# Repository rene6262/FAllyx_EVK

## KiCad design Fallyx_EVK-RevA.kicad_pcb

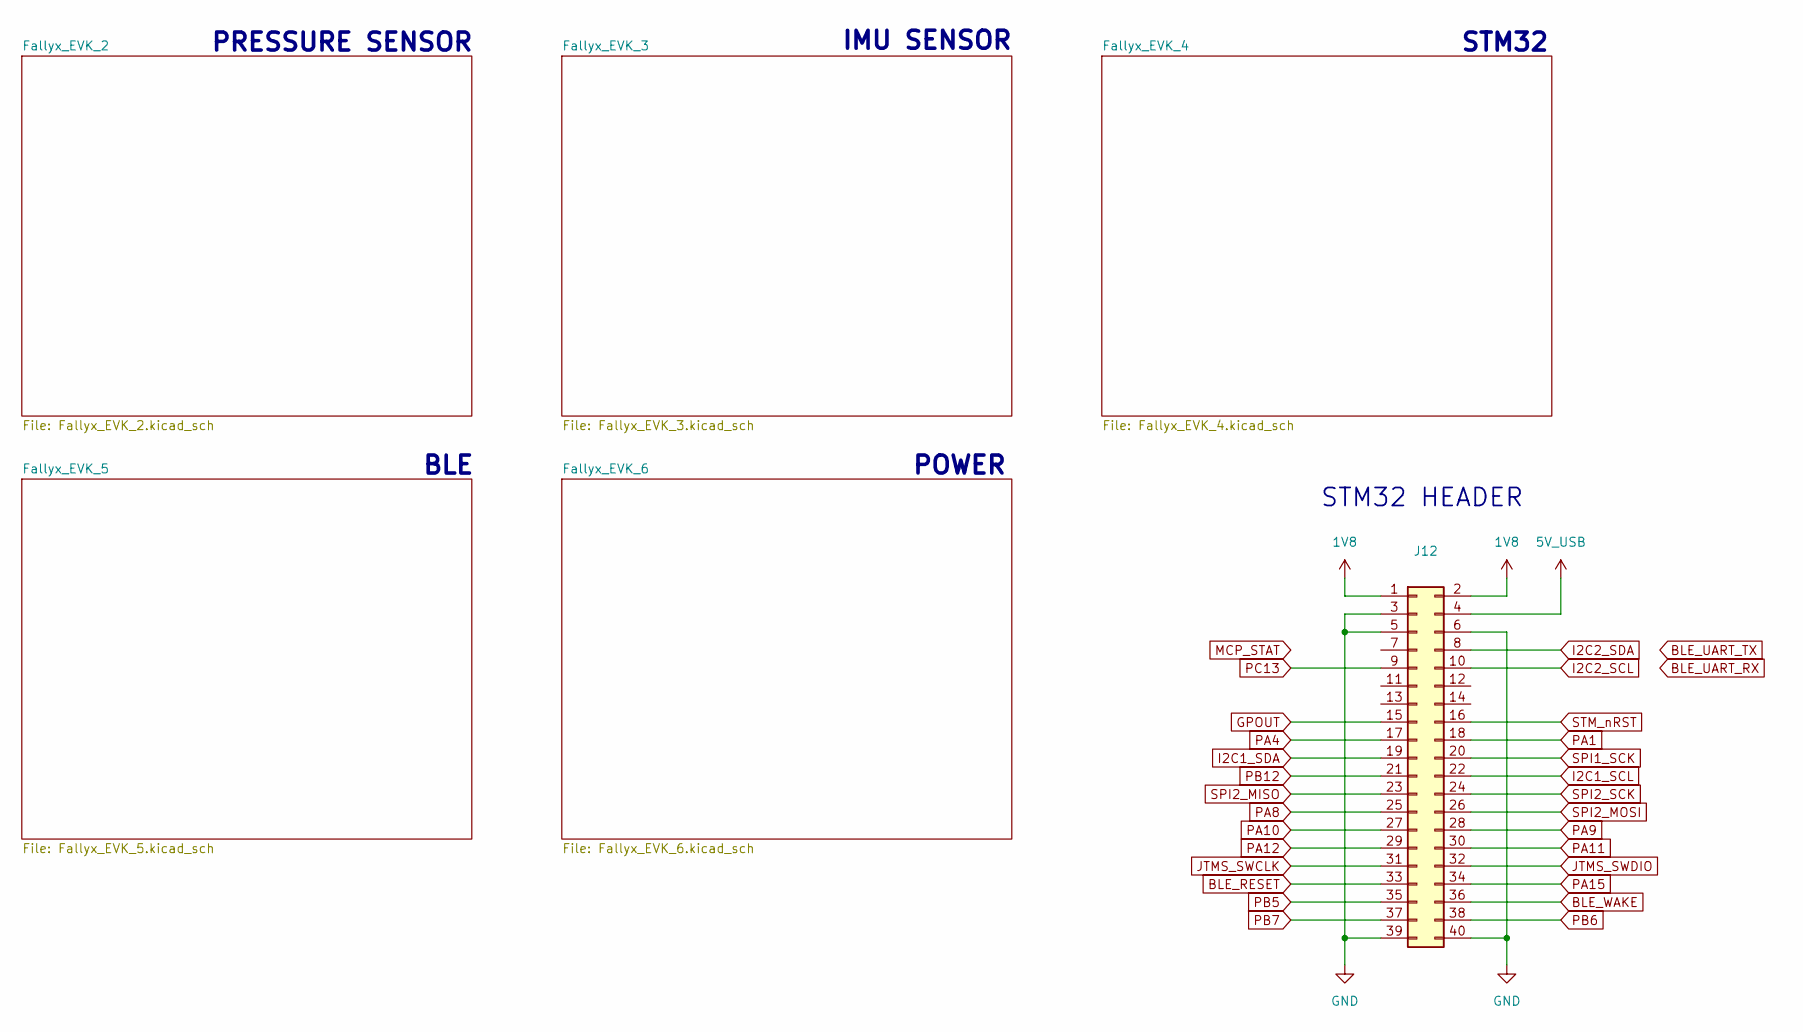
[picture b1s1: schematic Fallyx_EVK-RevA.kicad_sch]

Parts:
J12: Conn_02x20_Odd_Even; PinHeader_2x20_P2.54mm_Vertical

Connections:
1V8: J12.1, J12.2; also elsewhere on the board
5V_USB: J12.4; also elsewhere on the board
BLE_RESET: J12.33; also elsewhere on the board
BLE_UART_RX: J12.10; also elsewhere on the board
BLE_UART_TX: J12.8; also elsewhere on the board
BLE_WAKE: J12.36; also elsewhere on the board
GND: J12.3, J12.5, J12.6, J12.39, J12.40; also elsewhere on the board
GPOUT: J12.15; also elsewhere on the board
I2C1_SCL: J12.22; also elsewhere on the board
I2C1_SDA: J12.19; also elsewhere on the board
JTMS_SWCLK: J12.31; also elsewhere on the board
JTMS_SWDIO: J12.32; also elsewhere on the board
PA1: J12.18; also elsewhere on the board
PA4: J12.17; also elsewhere on the board
PA8: J12.25; also elsewhere on the board
PA9: J12.28; also elsewhere on the board
PA10: J12.27; also elsewhere on the board
PA11: J12.30; also elsewhere on the board
PA12: J12.29; also elsewhere on the board
PA15: J12.34; also elsewhere on the board
PB5: J12.35; also elsewhere on the board
PB6: J12.38; also elsewhere on the board
PB7: J12.37; also elsewhere on the board
PB12: J12.21; also elsewhere on the board
PC13: J12.9; also elsewhere on the board
SPI1_SCK: J12.20; also elsewhere on the board
SPI2_MISO: J12.23; also elsewhere on the board
SPI2_MOSI: J12.26; also elsewhere on the board
SPI2_SCK: J12.24; also elsewhere on the board
STM_nRST: J12.16; also elsewhere on the board

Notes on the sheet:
STM32 HEADER
BLE
POWER
STM32
IMU SENSOR
PRESSURE SENSOR

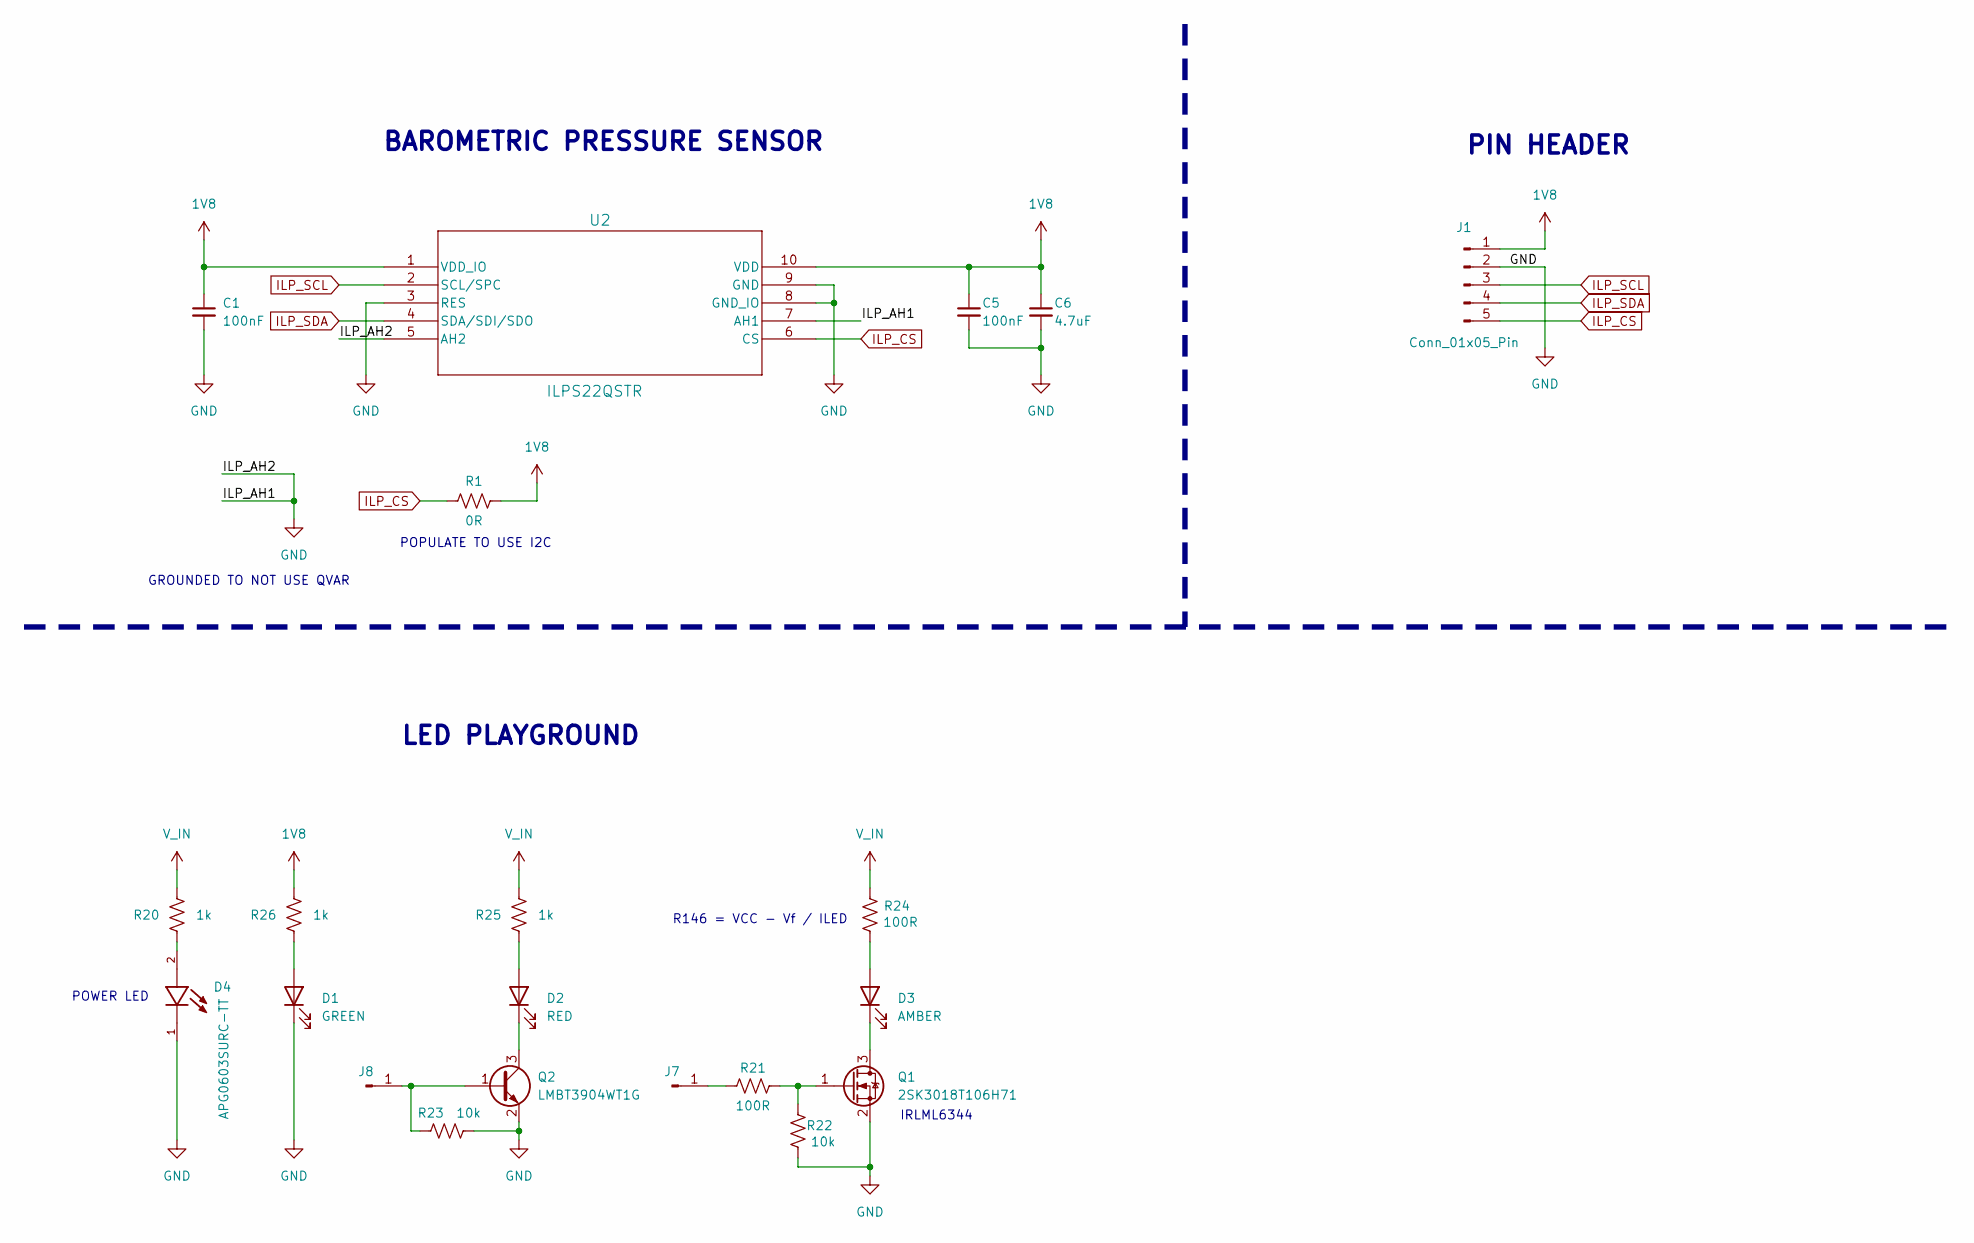
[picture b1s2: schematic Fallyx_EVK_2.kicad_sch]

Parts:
C1, C5: 100nF; C_0603_1608Metric
C6: 4.7uF; C_0603_1608Metric
D1: GREEN; LED_0603_1608Metric
D2: RED; LED_0603_1608Metric
D3: AMBER; LED_0603_1608Metric
D4: APG0603SURC-TT; LED_APG0603SURC-TT; PARTREV V.9B
J1: Conn_01x05_Pin; PinHeader_1x05_P2.54mm_Vertical
J7, J8: Conn_01x01_Pin; PinHeader_1x01_P2.54mm_Vertical
Q1: 2SK3018T106H71; SOT-323_SC-70
Q2: LMBT3904WT1G; SOT-23
R1: 0R; R_0805_2012Metric
R20, R25, R26: 1k; R_0402_1005Metric
R21, R24: 100R; R_0402_1005Metric
R22, R23: 10k; R_0402_1005Metric
U2: ILPS22QSTR; HLGA_10L_STM

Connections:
1V8: C1.1, C5.1, C6.1, J1.1, R1.2, R26.1, U2.1 (VDD_IO), U2.10 (VDD); also elsewhere on the board
GND: C1.2, C5.2, C6.2, D1.1 (K), D4.1, J1.2, Q1.2 (S), Q2.2 (E), R22.2, R23.1, U2.3 (RES), U2.5 (AH2), U2.7 (AH1), U2.8 (GND_IO), U2.9 (GND); also elsewhere on the board
ILP_CS: J1.5, R1.1, U2.6 (CS)
ILP_SCL: J1.3, U2.2 (SCL/SPC)
ILP_SDA: J1.4, U2.4 (SDA/SDI/SDO)
unnamed: D1.2 (A), R26.2
unnamed: D2.2 (A), R25.2
unnamed: D2.1 (K), Q2.3 (C)
unnamed: D3.2 (A), R24.2
unnamed: D3.1 (K), Q1.3 (D)
unnamed: D4.2, R20.2
unnamed: J7.1, R21.2
unnamed: J8.1, Q2.1 (B), R23.2
unnamed: Q1.1 (G), R21.1, R22.1
V_IN: R20.1, R24.1, R25.1; also elsewhere on the board

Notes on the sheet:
GROUNDED TO NOT USE QVAR
PIN HEADER
POPULATE TO USE I2C
IRLML6344
BAROMETRIC PRESSURE SENSOR
LED PLAYGROUND
POWER LED
R146 = VCC - Vf / ILED

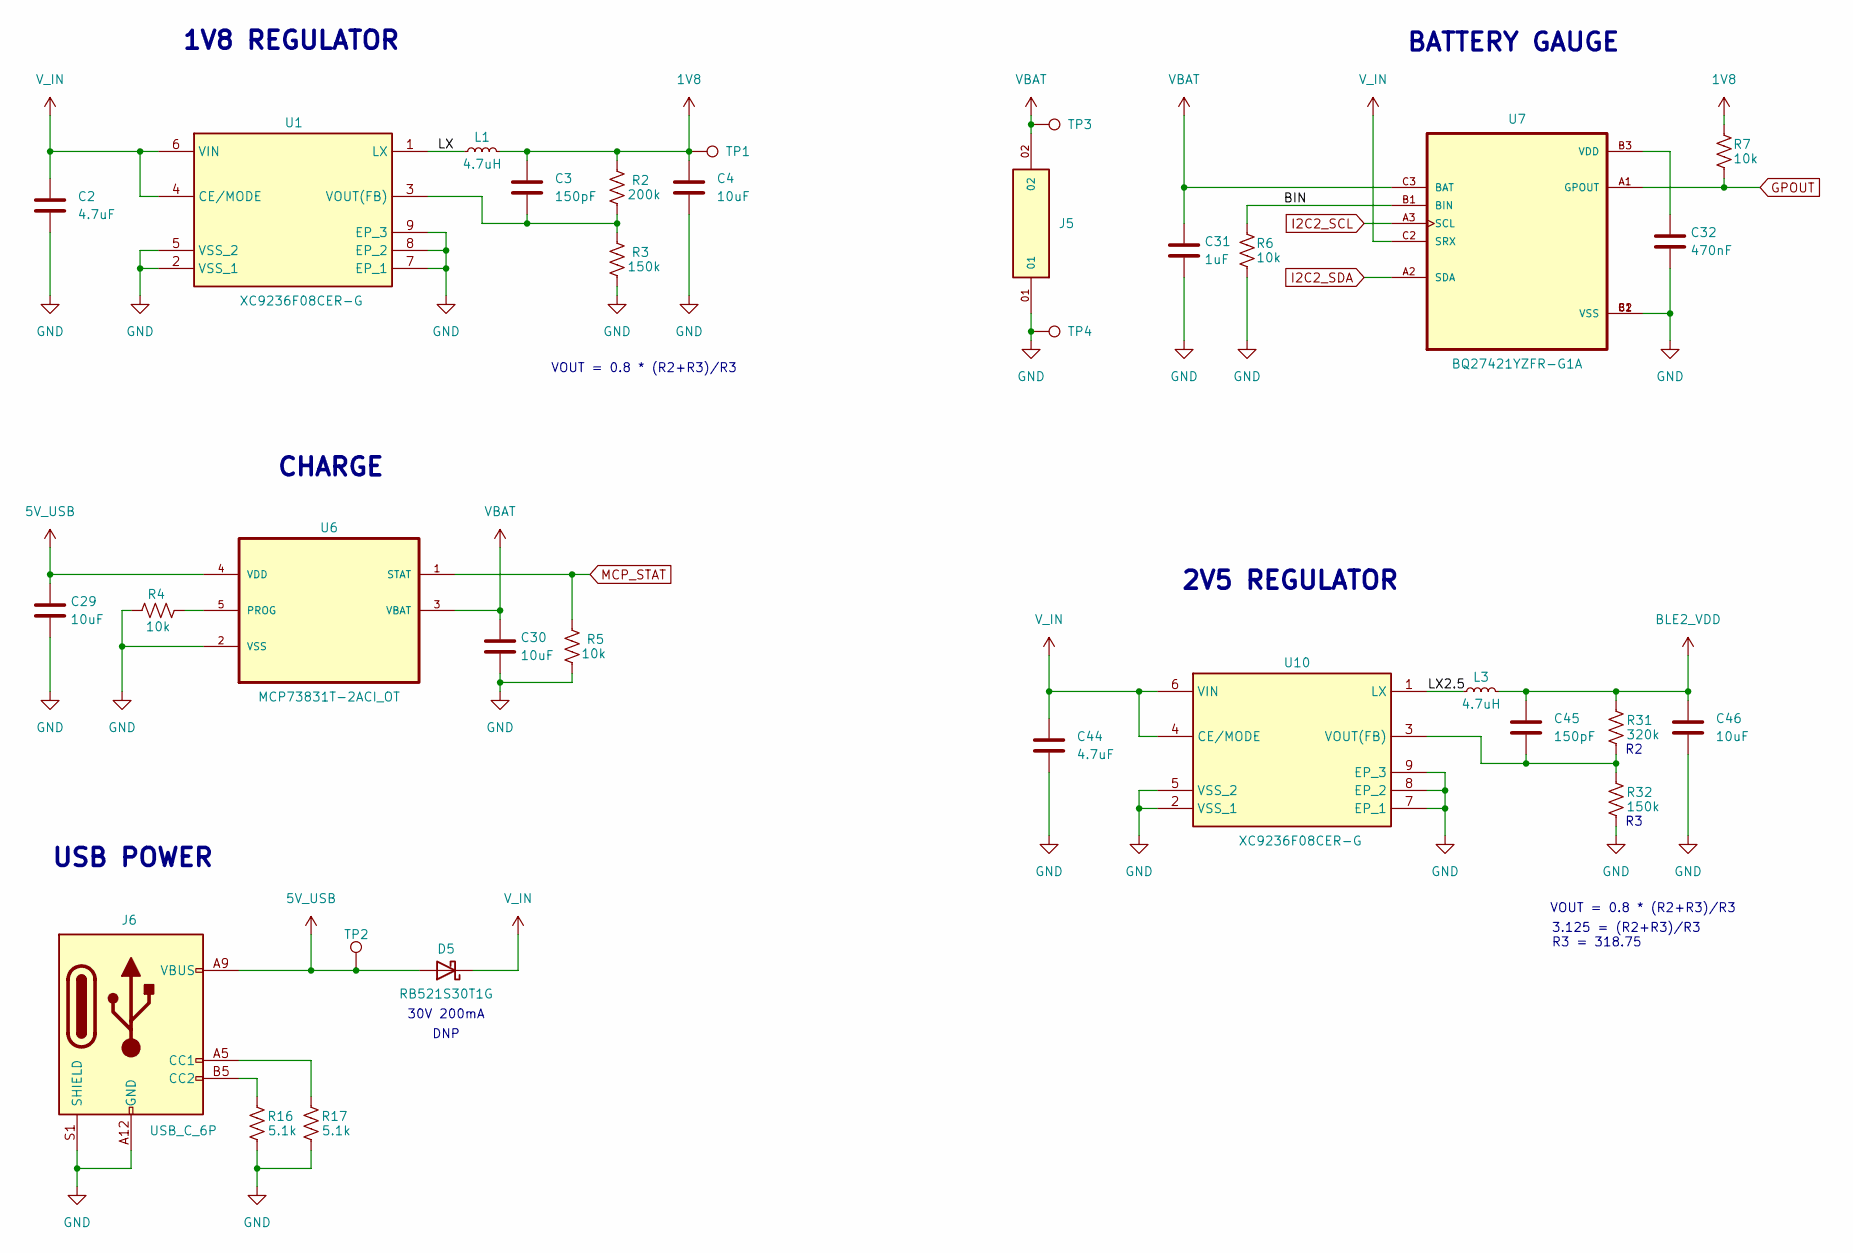
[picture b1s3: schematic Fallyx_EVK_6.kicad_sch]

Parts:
C2, C44: 4.7uF; C_0603_1608Metric
C3, C45: 150pF; C_0603_1608Metric
C4, C46: 10uF; C_0805_2012Metric
C29, C30: 10uF; C_0402_1005Metric
C31: 1uF; C_0402_1005Metric
C32: 470nF; C_0402_1005Metric
D5: RB521S30T1G; DIOM168X70N
J5: MTSW-101-X-X-D-X; SAMTEC_MTSW-101-X-X-D-X; PARTREV A
J6: USB_C_6P; USB_C_Receptacle_GCT_USB4135-GF-A_6P_TopMnt_Horizontal
L1, L3: 4.7uH; IND_TAIYO_NR3015_TAY
R2: 200k; R_0402_1005Metric
R3, R32: 150k; R_0402_1005Metric
R4, R5, R6, R7: 10k; R_0402_1005Metric
R16, R17: 5.1k; R_0402_1005Metric
R31: 320k; R_0402_1005Metric
TP1, TP2, TP3, TP4: TestPoint; TestPoint_Pad_D1.5mm
U1, U10: XC9236F08CER-G; XC9236F08CERG; Mouser Part Number 865-XC9236F08CER-G
U6: MCP73831T-2ACI_OT; SOT95P280X145-5N; MPN MCP73831T-2ACI/OT
U7: BQ27421YZFR-G1A; IC_BQ27421YZFR-G1A

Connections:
1V8: C3.1, C4.1, L1.2, R2.2, R7.2, TP1.1; also elsewhere on the board
5V_USB: C29.1, D5.2 (A), J6.A9 (VBUS), J6.B9 (VBUS), TP2.1, U6.4 (VDD); also elsewhere on the board
/Fallyx_EVK_6/BIN: R6.2, U7.B1 (BIN)
/Fallyx_EVK_6/LX: L1.1, U1.1 (LX)
/Fallyx_EVK_6/LX2.5: L3.1, U10.1 (LX)
BLE2_VDD: C45.1, C46.1, L3.2, R31.2; also elsewhere on the board
BLE_UART_RX: U7.A3 (SCL); also elsewhere on the board
BLE_UART_TX: U7.A2 (SDA); also elsewhere on the board
GND: C2.2, C4.2, C29.2, C30.2, C31.2, C32.2, C44.2, C46.2, J5.01, J6.A12 (GND), J6.B12 (GND), J6.S1 (SHIELD), R3.1, R4.2, R5.1, R6.1, R16.1, R17.1, R32.1, TP4.1, U1.2 (VSS_1), U1.5 (VSS_2), U1.7 (EP_1), U1.8 (EP_2), U1.9 (EP_3), U6.2 (VSS), U7.B2 (VSS), U7.C1 (VSS), U10.2 (VSS_1), U10.5 (VSS_2), U10.7 (EP_1), U10.8 (EP_2), U10.9 (EP_3); also elsewhere on the board
GPOUT: R7.1, U7.A1 (GPOUT); also elsewhere on the board
MCP_STAT: R5.2, U6.1 (STAT); also elsewhere on the board
unnamed: J6.A5 (CC1), R17.2
unnamed: J6.B5 (CC2), R16.2
unnamed: C3.2, R2.1, R3.2, U1.3 (VOUT(FB))
unnamed: R4.1, U6.5 (PROG)
unnamed: C32.1, U7.B3 (VDD)
unnamed: C45.2, R31.1, R32.2, U10.3 (VOUT(FB))
VBAT: C30.1, C31.1, J5.02, TP3.1, U6.3 (VBAT), U7.C3 (BAT); also elsewhere on the board
V_IN: C2.1, C44.1, D5.1 (K), U1.4 (CE/MODE), U1.6 (VIN), U7.C2 (SRX), U10.4 (CE/MODE), U10.6 (VIN); also elsewhere on the board

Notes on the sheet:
USB POWER
VOUT = 0.8 * (R2+R3)/R3
30V 200mA
1V8 REGULATOR
DNP
BATTERY GAUGE
3.125 = (R2+R3)/R3 R3 = 318.75
CHARGE
2V5 REGULATOR

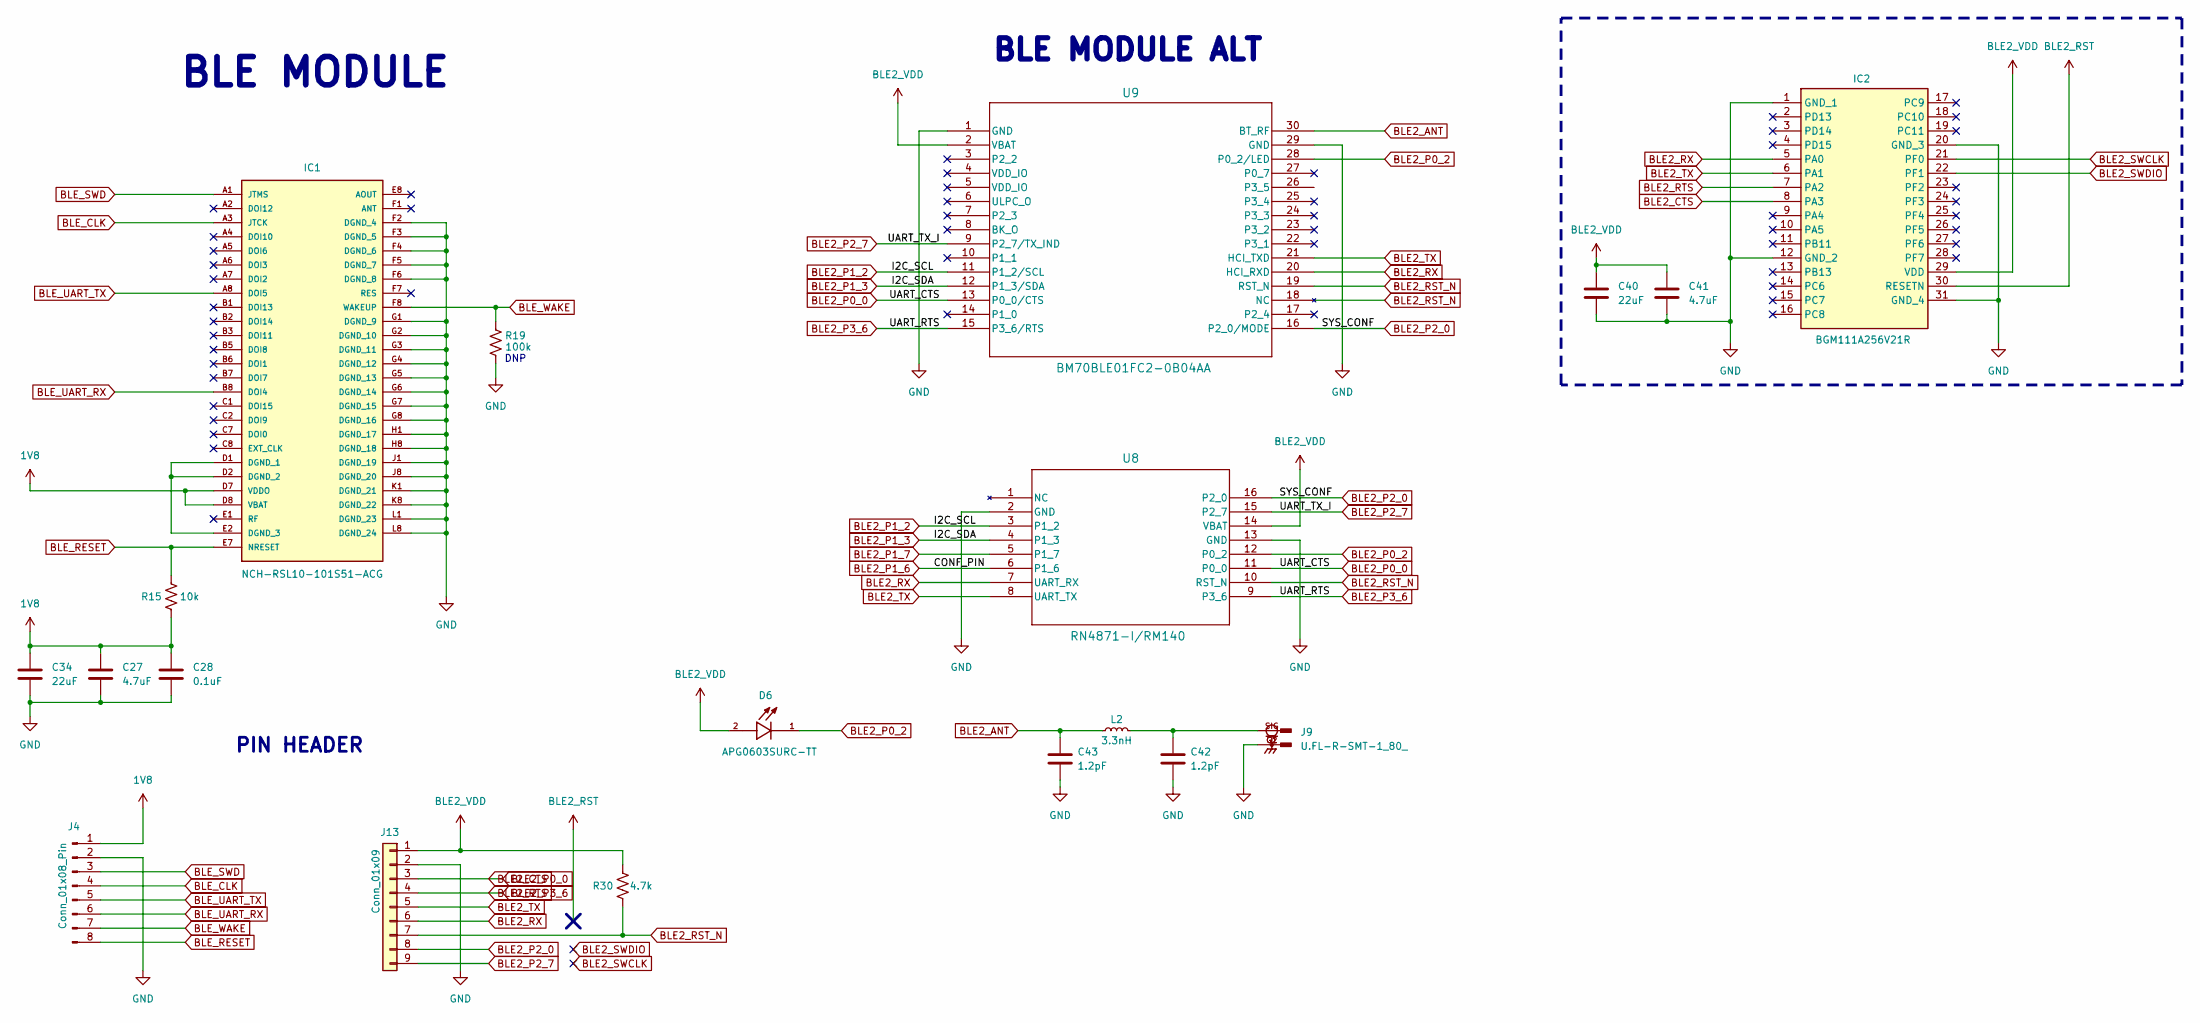
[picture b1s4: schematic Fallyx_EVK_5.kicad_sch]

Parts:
C27, C41: 4.7uF; C_0603_1608Metric
C28: 0.1uF; C_0402_1005Metric
C34, C40: 22uF; C_0603_1608Metric
C42, C43: 1.2pF; C_0402_1005Metric
D6: APG0603SURC-TT; LED_APG0603SURC-TT; PARTREV V.9B
IC1: NCH-RSL10-101S51-ACG; NCHRSL10101S51ACG; Mouser_Part_Number 863-NCHRSL1010S51ACG
IC2: BGM111A256V21R; Mouser Part Number 634-BGM111A256V21R
J4: Conn_01x08_Pin; PinHeader_1x08_P2.54mm_Vertical
J9: U.FL-R-SMT-1_80_; HIROSE_U.FL-R-SMT-1_80_; PARTREV Jul.1.2022
J13: Conn_01x09; PinHeader_1x09_P2.54mm_Vertical
L2: 3.3nH; L_0402_1005Metric
R15: 10k; R_0402_1005Metric
R19: 100k; R_0402_1005Metric
R30: 4.7k; R_0402_1005Metric
U8: RN4871-I/RM140; Microchip_RN4871
U9: BM70BLE01FC2-0B04AA; BM70BLE01FC2_MCH

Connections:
1V8: C27.1, C28.1, C34.1, IC1.D7 (VDDO), IC1.D8 (VBAT), J4.1, R15.1; also elsewhere on the board
BLE2_ANT: C43.1, L2.1, U9.30 (BT_RF)
BLE2_CTS: IC2.8 (PA3), J13.3, U8.11 (P0_0), U9.13 (P0_0/CTS)
BLE2_P0_2: D6.1, U8.12 (P0_2), U9.28 (P0_2/LED)
BLE2_P1_2: U8.3 (P1_2), U9.11 (P1_2/SCL)
BLE2_P1_3: U8.4 (P1_3), U9.12 (P1_3/SDA)
BLE2_P1_6: U8.6 (P1_6)
BLE2_P1_7: U8.5 (P1_7)
BLE2_P2_0: J13.8, U8.16 (P2_0), U9.16 (P2_0/MODE)
BLE2_P2_7: J13.9, U8.15 (P2_7), U9.9 (P2_7/TX_IND)
BLE2_P3_6: IC2.7 (PA2), J13.4, U8.9 (P3_6), U9.15 (P3_6/RTS)
BLE2_RST_N: J13.7, R30.1, U8.10 (RST_N), U9.18 (NC), U9.19 (RST_N)
BLE2_RX: IC2.5 (PA0), J13.6, U8.7 (UART_RX), U9.20 (HCI_RXD)
BLE2_TX: IC2.6 (PA1), J13.5, U8.8 (UART_TX), U9.21 (HCI_TXD)
BLE2_VDD: C40.1, C41.1, D6.2, IC2.29 (VDD), J13.1, R30.2, U8.14 (VBAT), U9.2 (VBAT); also elsewhere on the board
BLE_CLK: IC1.A3 (JTCK), J4.4
BLE_RESET: IC1.E7 (NRESET), J4.8, R15.2; also elsewhere on the board
BLE_SWD: IC1.A1 (JTMS), J4.3
BLE_UART_RX: IC1.B8 (DOI4), J4.6; also elsewhere on the board
BLE_UART_TX: IC1.A8 (DOI5), J4.5; also elsewhere on the board
BLE_WAKE: IC1.F8 (WAKEUP), J4.7, R19.2; also elsewhere on the board
GND: C27.2, C28.2, C34.2, C40.2, C41.2, C42.2, C43.2, IC1.F2 (DGND_4), IC1.F3 (DGND_5), IC1.F4 (DGND_6), IC1.F5 (DGND_7), IC1.F6 (DGND_8), IC1.G1 (DGND_9), IC1.G2 (DGND_10), IC1.G3 (DGND_11), IC1.G4 (DGND_12), IC1.G5 (DGND_13), IC1.G6 (DGND_14), IC1.G7 (DGND_15), IC1.G8 (DGND_16), IC1.H1 (DGND_17), IC1.H8 (DGND_18), IC1.J1 (DGND_19), IC1.J8 (DGND_20), IC1.K1 (DGND_21), IC1.K8 (DGND_22), IC1.L1 (DGND_23), IC1.L8 (DGND_24), IC2.1 (GND_1), IC2.12 (GND_2), IC2.20 (GND_3), IC2.31 (GND_4), J4.2, J9.G1, J9.G2, J13.2, R19.1, U8.2 (GND), U8.13 (GND), U9.1 (GND), U9.29 (GND); also elsewhere on the board
unnamed: C42.1, J9.SIG, L2.2
unnamed: IC1.D1 (DGND_1), IC1.D2 (DGND_2), IC1.E2 (DGND_3)

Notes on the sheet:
PIN HEADER
DNP
BLE MODULE
BLE MODULE ALT

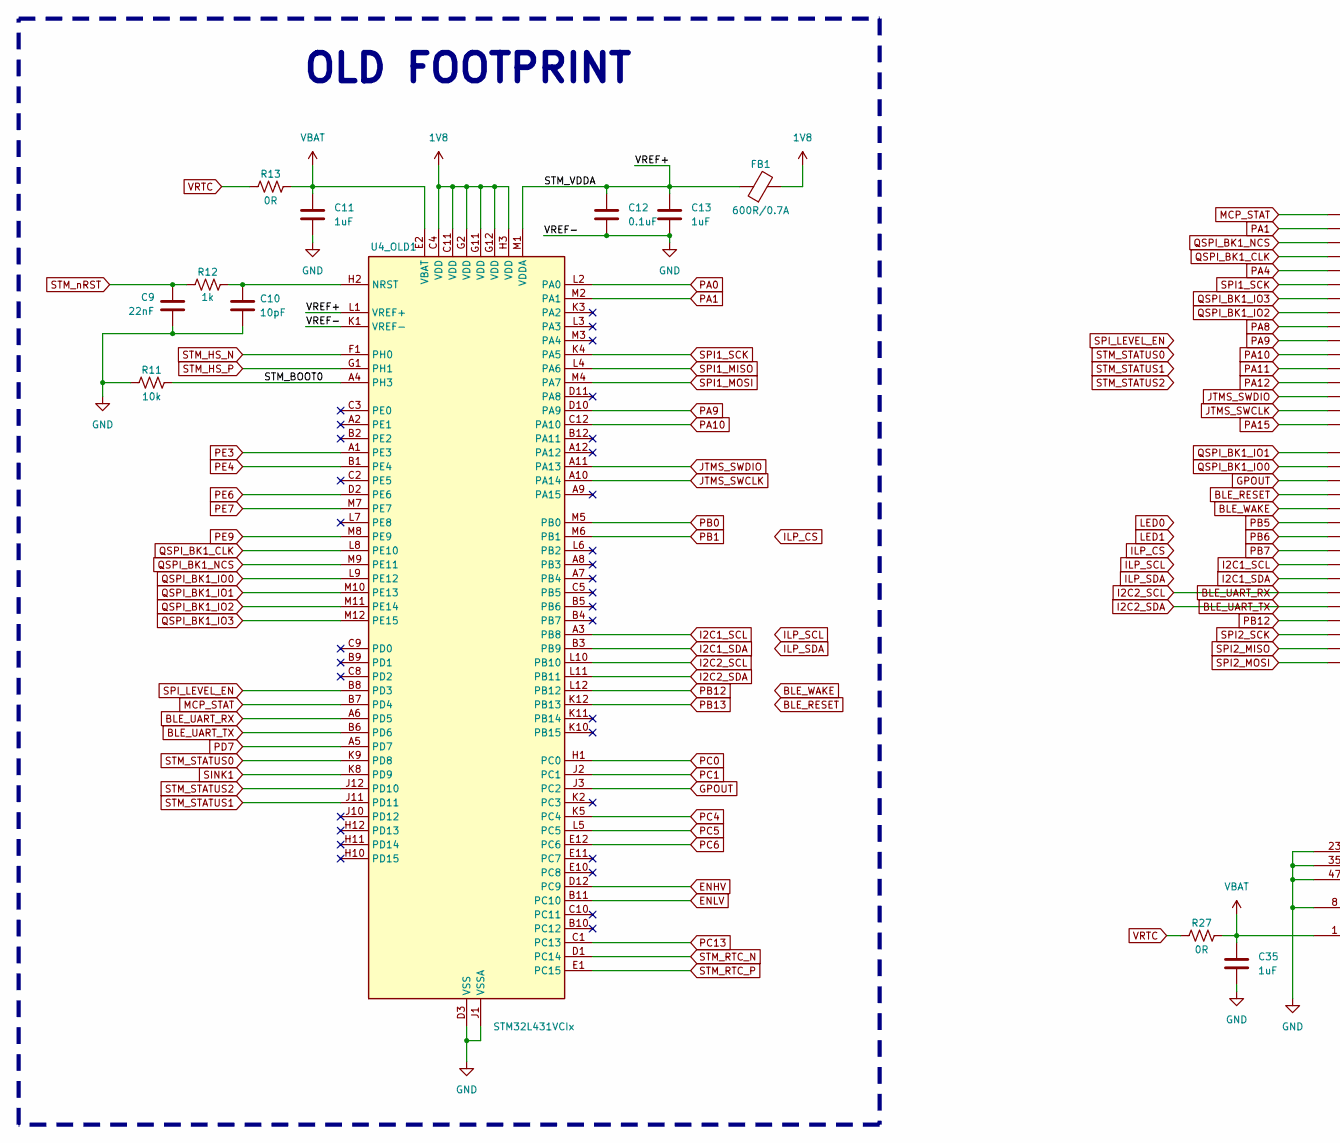
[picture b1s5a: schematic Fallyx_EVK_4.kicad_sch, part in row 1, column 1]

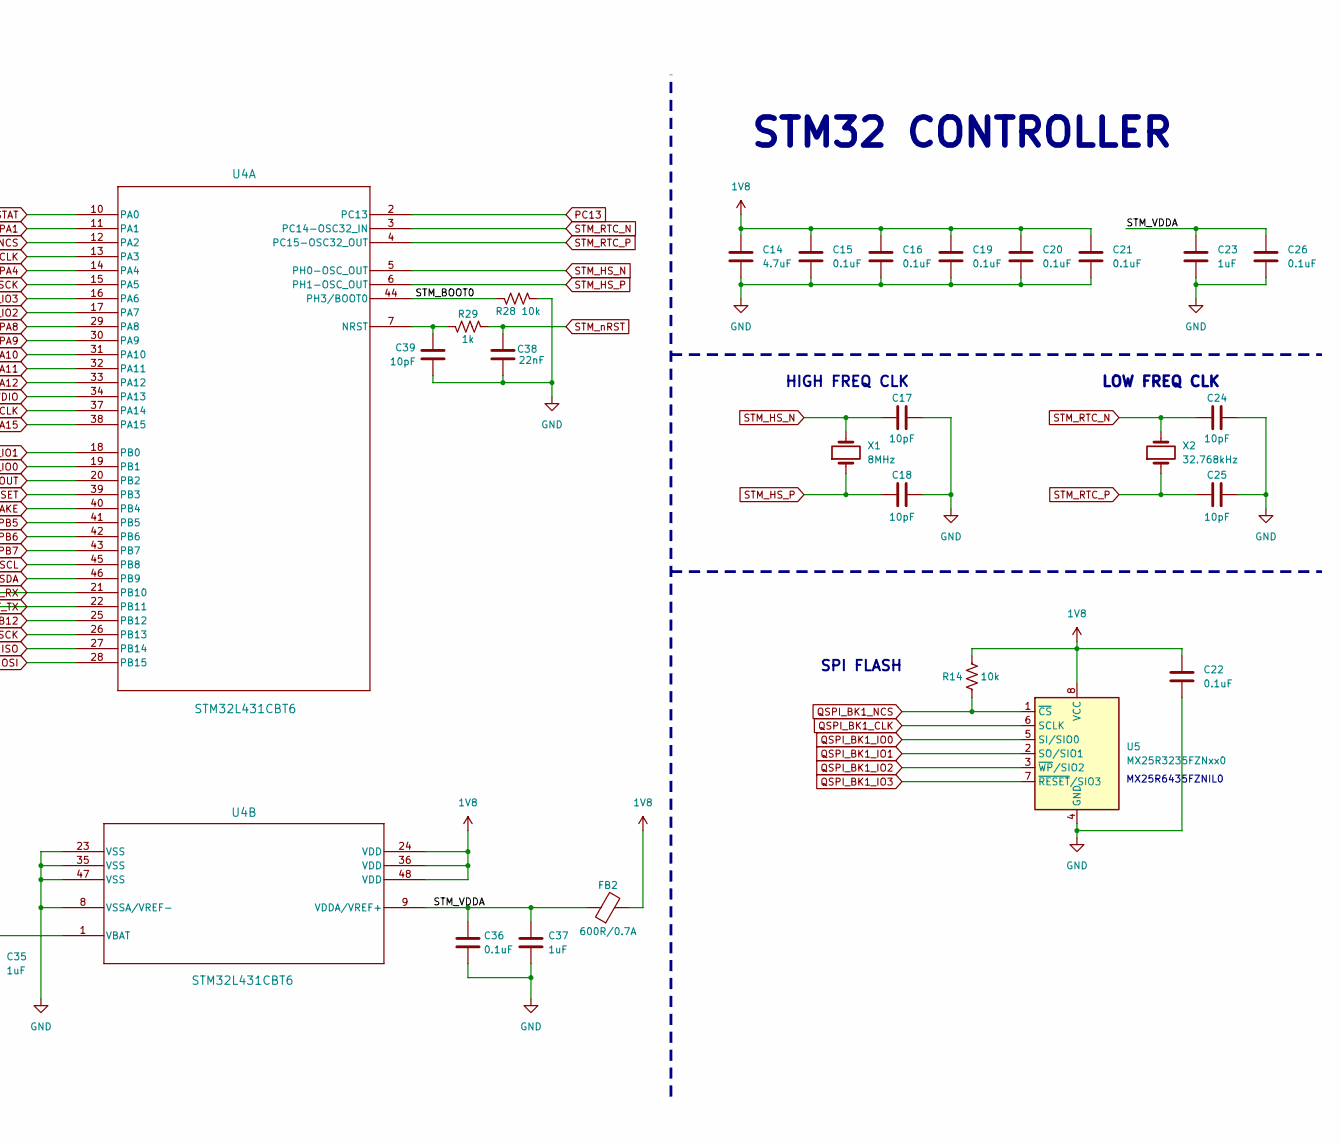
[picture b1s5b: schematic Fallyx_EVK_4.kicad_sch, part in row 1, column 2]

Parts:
C9, C38: 22nF; C_0402_1005Metric
C10, C17, C18, C24, C25, C39: 10pF; C_0402_1005Metric
C11, C13, C23, C35, C37: 1uF; C_0402_1005Metric
C12, C15, C16, C19, C20, C21, C22, C26, C36: 0.1uF; C_0402_1005Metric
C14: 4.7uF; C_0603_1608Metric
FB1: 600R/0.7A
FB2: 600R/0.7A; R_0402_1005Metric
R11, R14, R28: 10k; R_0402_1005Metric
R12, R29: 1k; R_0402_1005Metric
R13, R27: 0R; R_0805_2012Metric
U4: STM32L431CBT6; LQFP-48
U4_OLD1: STM32L431VCIx; UFBGA-100_7x7mm_Layout12x12_P0.5mm
U5: MX25R3235FZNxx0; WSON-8-1EP_6x5mm_P1.27mm_EP3.4x4mm
X1: 8MHz; XTAL_ECS-320-CDX-2094
X2: 32.768kHz; XTAL_CM9V-T1A-32.768KHZ-7PF-100PPM-TA-QC

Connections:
1V8: C14.1, C15.1, C16.1, C19.1, C20.1, C21.1, C22.1, FB1.2, FB2.2, R14.2, U4.24 (VDD), U4.36 (VDD), U4.48 (VDD), U4_OLD1.C4 (VDD), U4_OLD1.C11 (VDD), U4_OLD1.G2 (VDD), U4_OLD1.G11 (VDD), U4_OLD1.G12 (VDD), U4_OLD1.H3 (VDD), U5.8 (VCC); also elsewhere on the board
/Fallyx_EVK_4/STM_BOOT0: R11.2, R28.2, U4.44 (PH3/BOOT0), U4_OLD1.A4 (PH3)
/Fallyx_EVK_4/STM_VDDA: C12.1, C13.1, C23.1, C26.1, C36.1, C37.1, FB1.1, FB2.1, U4.9 (VDDA/VREF+), U4_OLD1.L1 (VREF+), U4_OLD1.M1 (VDDA)
BLE_RESET: U4.39 (PB3); also elsewhere on the board
BLE_UART_RX: U4.21 (PB10), U4_OLD1.A6 (PD5), U4_OLD1.L10 (PB10); also elsewhere on the board
BLE_UART_TX: U4.22 (PB11), U4_OLD1.B6 (PD6), U4_OLD1.L11 (PB11); also elsewhere on the board
BLE_WAKE: U4.40 (PB4); also elsewhere on the board
GND: C9.2, C10.2, C11.2, C12.2, C13.2, C14.2, C15.2, C16.2, C17.2, C18.2, C19.2, C20.2, C21.2, C22.2, C23.2, C24.2, C25.2, C26.2, C35.2, C36.2, C37.2, C38.2, C39.2, R11.1, R28.1, U4.8 (VSSA/VREF-), U4.23 (VSS), U4.35 (VSS), U4.47 (VSS), U4_OLD1.D3 (VSS), U4_OLD1.E3 (VSS), U4_OLD1.F2 (VSS), U4_OLD1.F11 (VSS), U4_OLD1.F12 (VSS), U4_OLD1.J1 (VSSA), U4_OLD1.K1 (VREF-), U5.4 (GND), U5.9 (GND); also elsewhere on the board
GPOUT: U4.20 (PB2), U4_OLD1.J3 (PC2); also elsewhere on the board
I2C1_SCL: U4.45 (PB8), U4_OLD1.A3 (PB8); also elsewhere on the board
I2C1_SDA: U4.46 (PB9), U4_OLD1.B3 (PB9); also elsewhere on the board
JTMS_SWCLK: U4.37 (PA14), U4_OLD1.A10 (PA14); also elsewhere on the board
JTMS_SWDIO: U4.34 (PA13), U4_OLD1.A11 (PA13); also elsewhere on the board
MCP_STAT: U4.10 (PA0), U4_OLD1.B7 (PD4); also elsewhere on the board
unnamed: C10.1, R12.2, U4_OLD1.H2 (NRST)
unnamed: C39.1, R29.2, U4.7 (NRST)
PA1: U4.11 (PA1), U4_OLD1.M2 (PA1); also elsewhere on the board
PA4: U4.14 (PA4); also elsewhere on the board
PA8: U4.29 (PA8); also elsewhere on the board
PA9: U4.30 (PA9), U4_OLD1.D10 (PA9); also elsewhere on the board
PA10: U4.31 (PA10), U4_OLD1.C12 (PA10); also elsewhere on the board
PA11: U4.32 (PA11); also elsewhere on the board
PA12: U4.33 (PA12); also elsewhere on the board
PA15: U4.38 (PA15); also elsewhere on the board
PB5: U4.41 (PB5); also elsewhere on the board
PB6: U4.42 (PB6); also elsewhere on the board
PB7: U4.43 (PB7); also elsewhere on the board
PB12: U4.25 (PB12), U4_OLD1.L12 (PB12); also elsewhere on the board
PC13: U4.2 (PC13), U4_OLD1.C1 (PC13); also elsewhere on the board
QSPI_BK1_CLK: U4.13 (PA3), U4_OLD1.L8 (PE10), U5.6 (SCLK)
QSPI_BK1_IO0: U4.19 (PB1), U4_OLD1.L9 (PE12), U5.5 (SI/SIO0)
QSPI_BK1_IO1: U4.18 (PB0), U4_OLD1.M10 (PE13), U5.2 (SO/SIO1)
QSPI_BK1_IO2: U4.17 (PA7), U4_OLD1.M11 (PE14), U5.3 (~WP/SIO2)
QSPI_BK1_IO3: U4.16 (PA6), U4_OLD1.M12 (PE15), U5.7 (~RESET/SIO3)
QSPI_BK1_NCS: R14.1, U4.12 (PA2), U4_OLD1.M9 (PE11), U5.1 (~CS)
SPI1_SCK: U4.15 (PA5), U4_OLD1.K4 (PA5); also elsewhere on the board
SPI2_MISO: U4.27 (PB14); also elsewhere on the board
SPI2_MOSI: U4.28 (PB15); also elsewhere on the board
SPI2_SCK: U4.26 (PB13); also elsewhere on the board
STM_HS_N: C17.1, U4.5 (PH0-OSC_OUT), U4_OLD1.F1 (PH0), X1.2
STM_HS_P: C18.1, U4.6 (PH1-OSC_OUT), U4_OLD1.G1 (PH1), X1.1
STM_RTC_N: C24.1, U4.3 (PC14-OSC32_IN), U4_OLD1.D1 (PC14), X2.2
STM_RTC_P: C25.1, U4.4 (PC15-OSC32_OUT), U4_OLD1.E1 (PC15), X2.1
STM_nRST: C9.1, C38.1, R12.1, R29.1; also elsewhere on the board
VBAT: C11.1, C35.1, R13.2, R27.2, U4.1 (VBAT), U4_OLD1.E2 (VBAT); also elsewhere on the board
VRTC: R13.1, R27.1

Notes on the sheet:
OLD FOOTPRINT
HIGH FREQ CLK
LOW FREQ CLK
MX25R6435FZNIL0
SPI FLASH
STM32 CONTROLLER

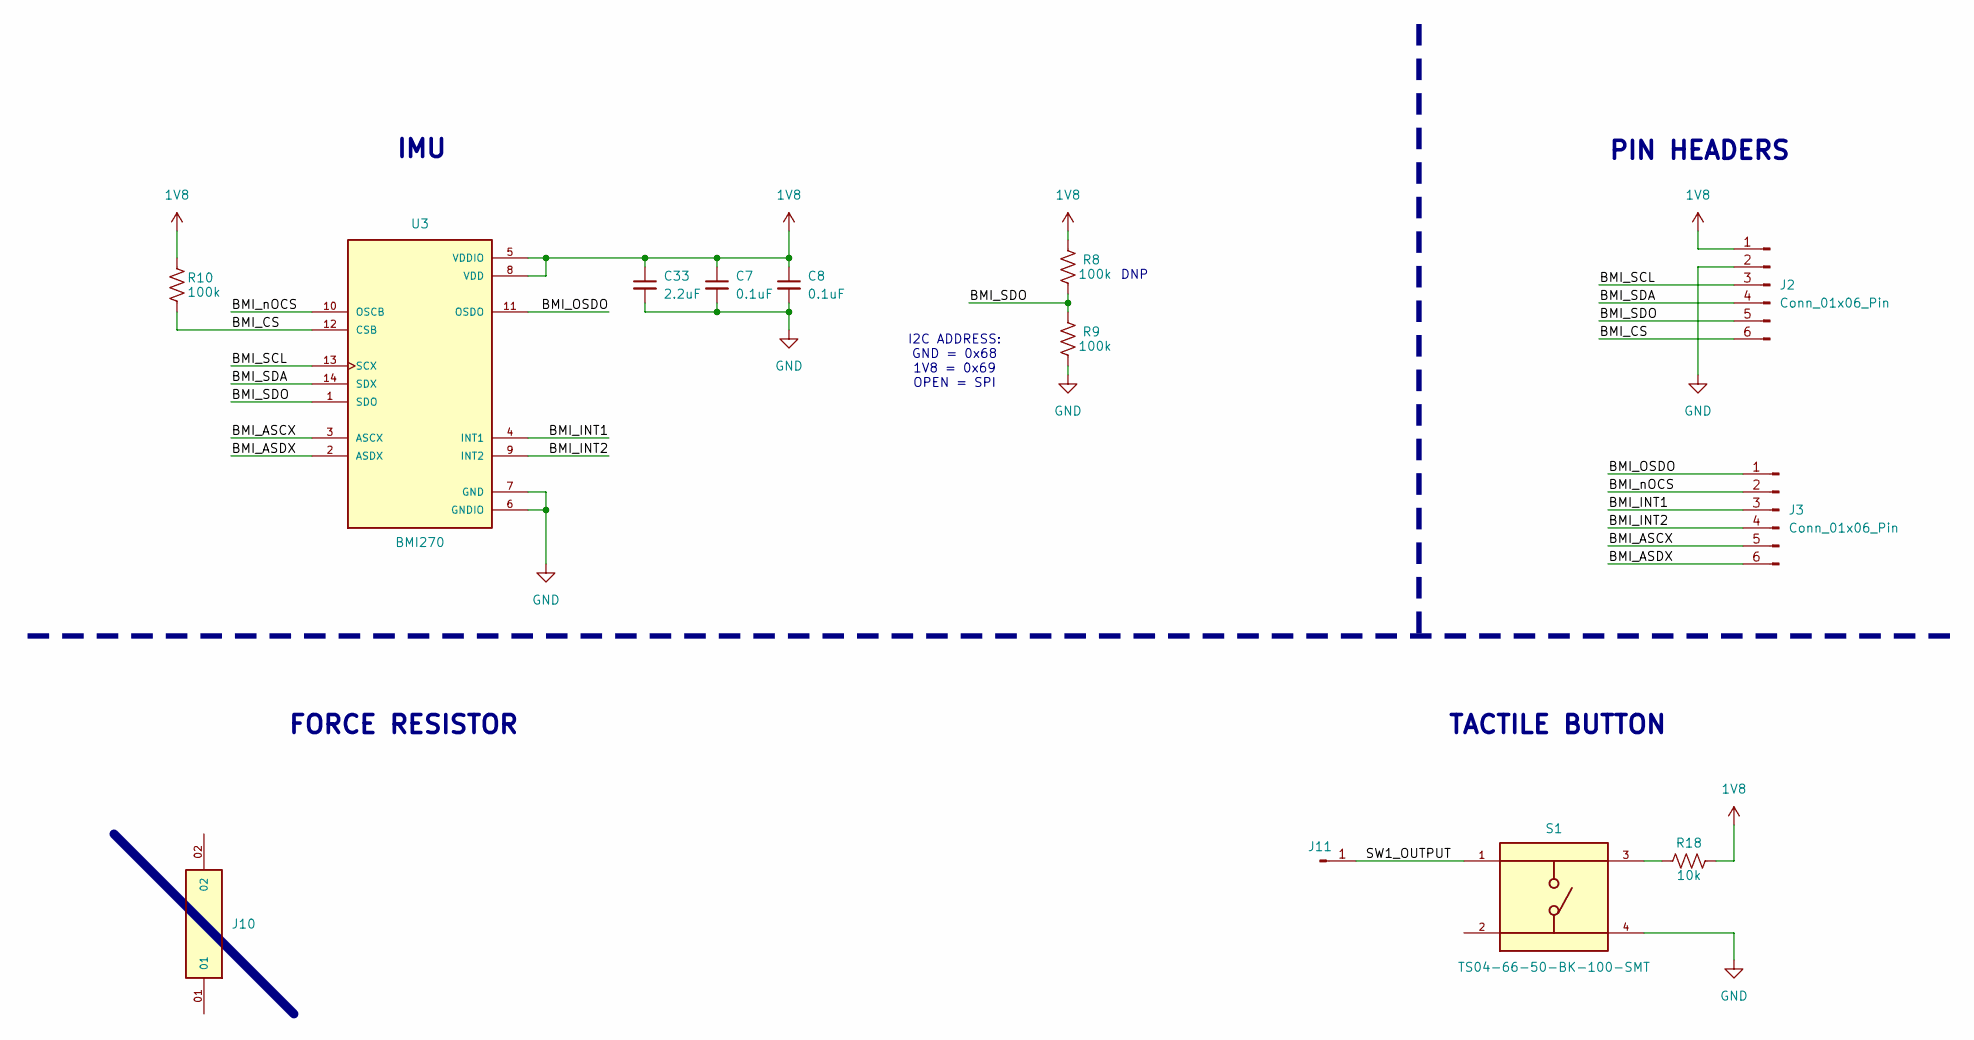
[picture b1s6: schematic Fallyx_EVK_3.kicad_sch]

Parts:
C7, C8: 0.1uF; C_0603_1608Metric
C33: 2.2uF; C_0603_1608Metric
J2, J3: Conn_01x06_Pin; PinHeader_1x06_P2.54mm_Vertical
J10: MTSW-101-X-X-D-X; SAMTEC_MTSW-101-X-X-D-X; PARTREV A
J11: Conn_01x01_Pin; PinHeader_1x01_P2.54mm_Vertical
R8, R9, R10: 100k; R_0402_1005Metric
R18: 10k; R_0402_1005Metric
S1: TS04-66-50-BK-100-SMT; SW_TS04-66-50-BK-100-SMT; PARTREV 1.0
U3: BMI270; XDCR_BMI270

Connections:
1V8: C7.1, C8.1, C33.1, J2.1, R8.2, R10.2, R18.1, U3.5 (VDDIO), U3.8 (VDD); also elsewhere on the board
/Fallyx_EVK_3/BMI_ASCX: J3.5, U3.3 (ASCX)
/Fallyx_EVK_3/BMI_ASDX: J3.6, U3.2 (ASDX)
/Fallyx_EVK_3/BMI_CS: J2.6, R10.1, U3.12 (CSB)
/Fallyx_EVK_3/BMI_INT1: J3.3, U3.4 (INT1)
/Fallyx_EVK_3/BMI_INT2: J3.4, U3.9 (INT2)
/Fallyx_EVK_3/BMI_OSDO: J3.1, U3.11 (OSDO)
/Fallyx_EVK_3/BMI_SCL: J2.3, U3.13 (SCX)
/Fallyx_EVK_3/BMI_SDA: J2.4, U3.14 (SDX)
/Fallyx_EVK_3/BMI_SDO: J2.5, R8.1, R9.2, U3.1 (SDO)
/Fallyx_EVK_3/BMI_nOCS: J3.2, U3.10 (OSCB)
/Fallyx_EVK_3/SW1_OUTPUT: J11.1, S1.1
GND: C7.2, C8.2, C33.2, J2.2, R9.1, S1.4, U3.6 (GNDIO), U3.7 (GND); also elsewhere on the board
unnamed: R18.2, S1.3

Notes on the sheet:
DNP
FORCE RESISTOR
I2C ADDRESS: GND = 0x68 1V8 = 0x69 OPEN = SPI
TACTILE BUTTON
PIN HEADERS
IMU
